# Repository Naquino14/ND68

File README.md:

# ND68
**ND68 MKL (Most keyless) Proto**

ND68 is a quest to design a custom 68% keyboard pcb powered by an RP2040, complete with per key RGB, hot-swappable keys, and a USB-C connector. 
We are in the prototyping phase, and if successful the prototype works as a macro pad.

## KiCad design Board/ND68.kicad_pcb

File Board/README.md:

# License for all subfolders of this one:

All files in subfolders of this one created by contrubutors of this repository are licensed under Creative Commons Attribution-NonCommercial-NoDerivatives (CC BY-NC-ND).

[Please view the license file here](LICENSE).

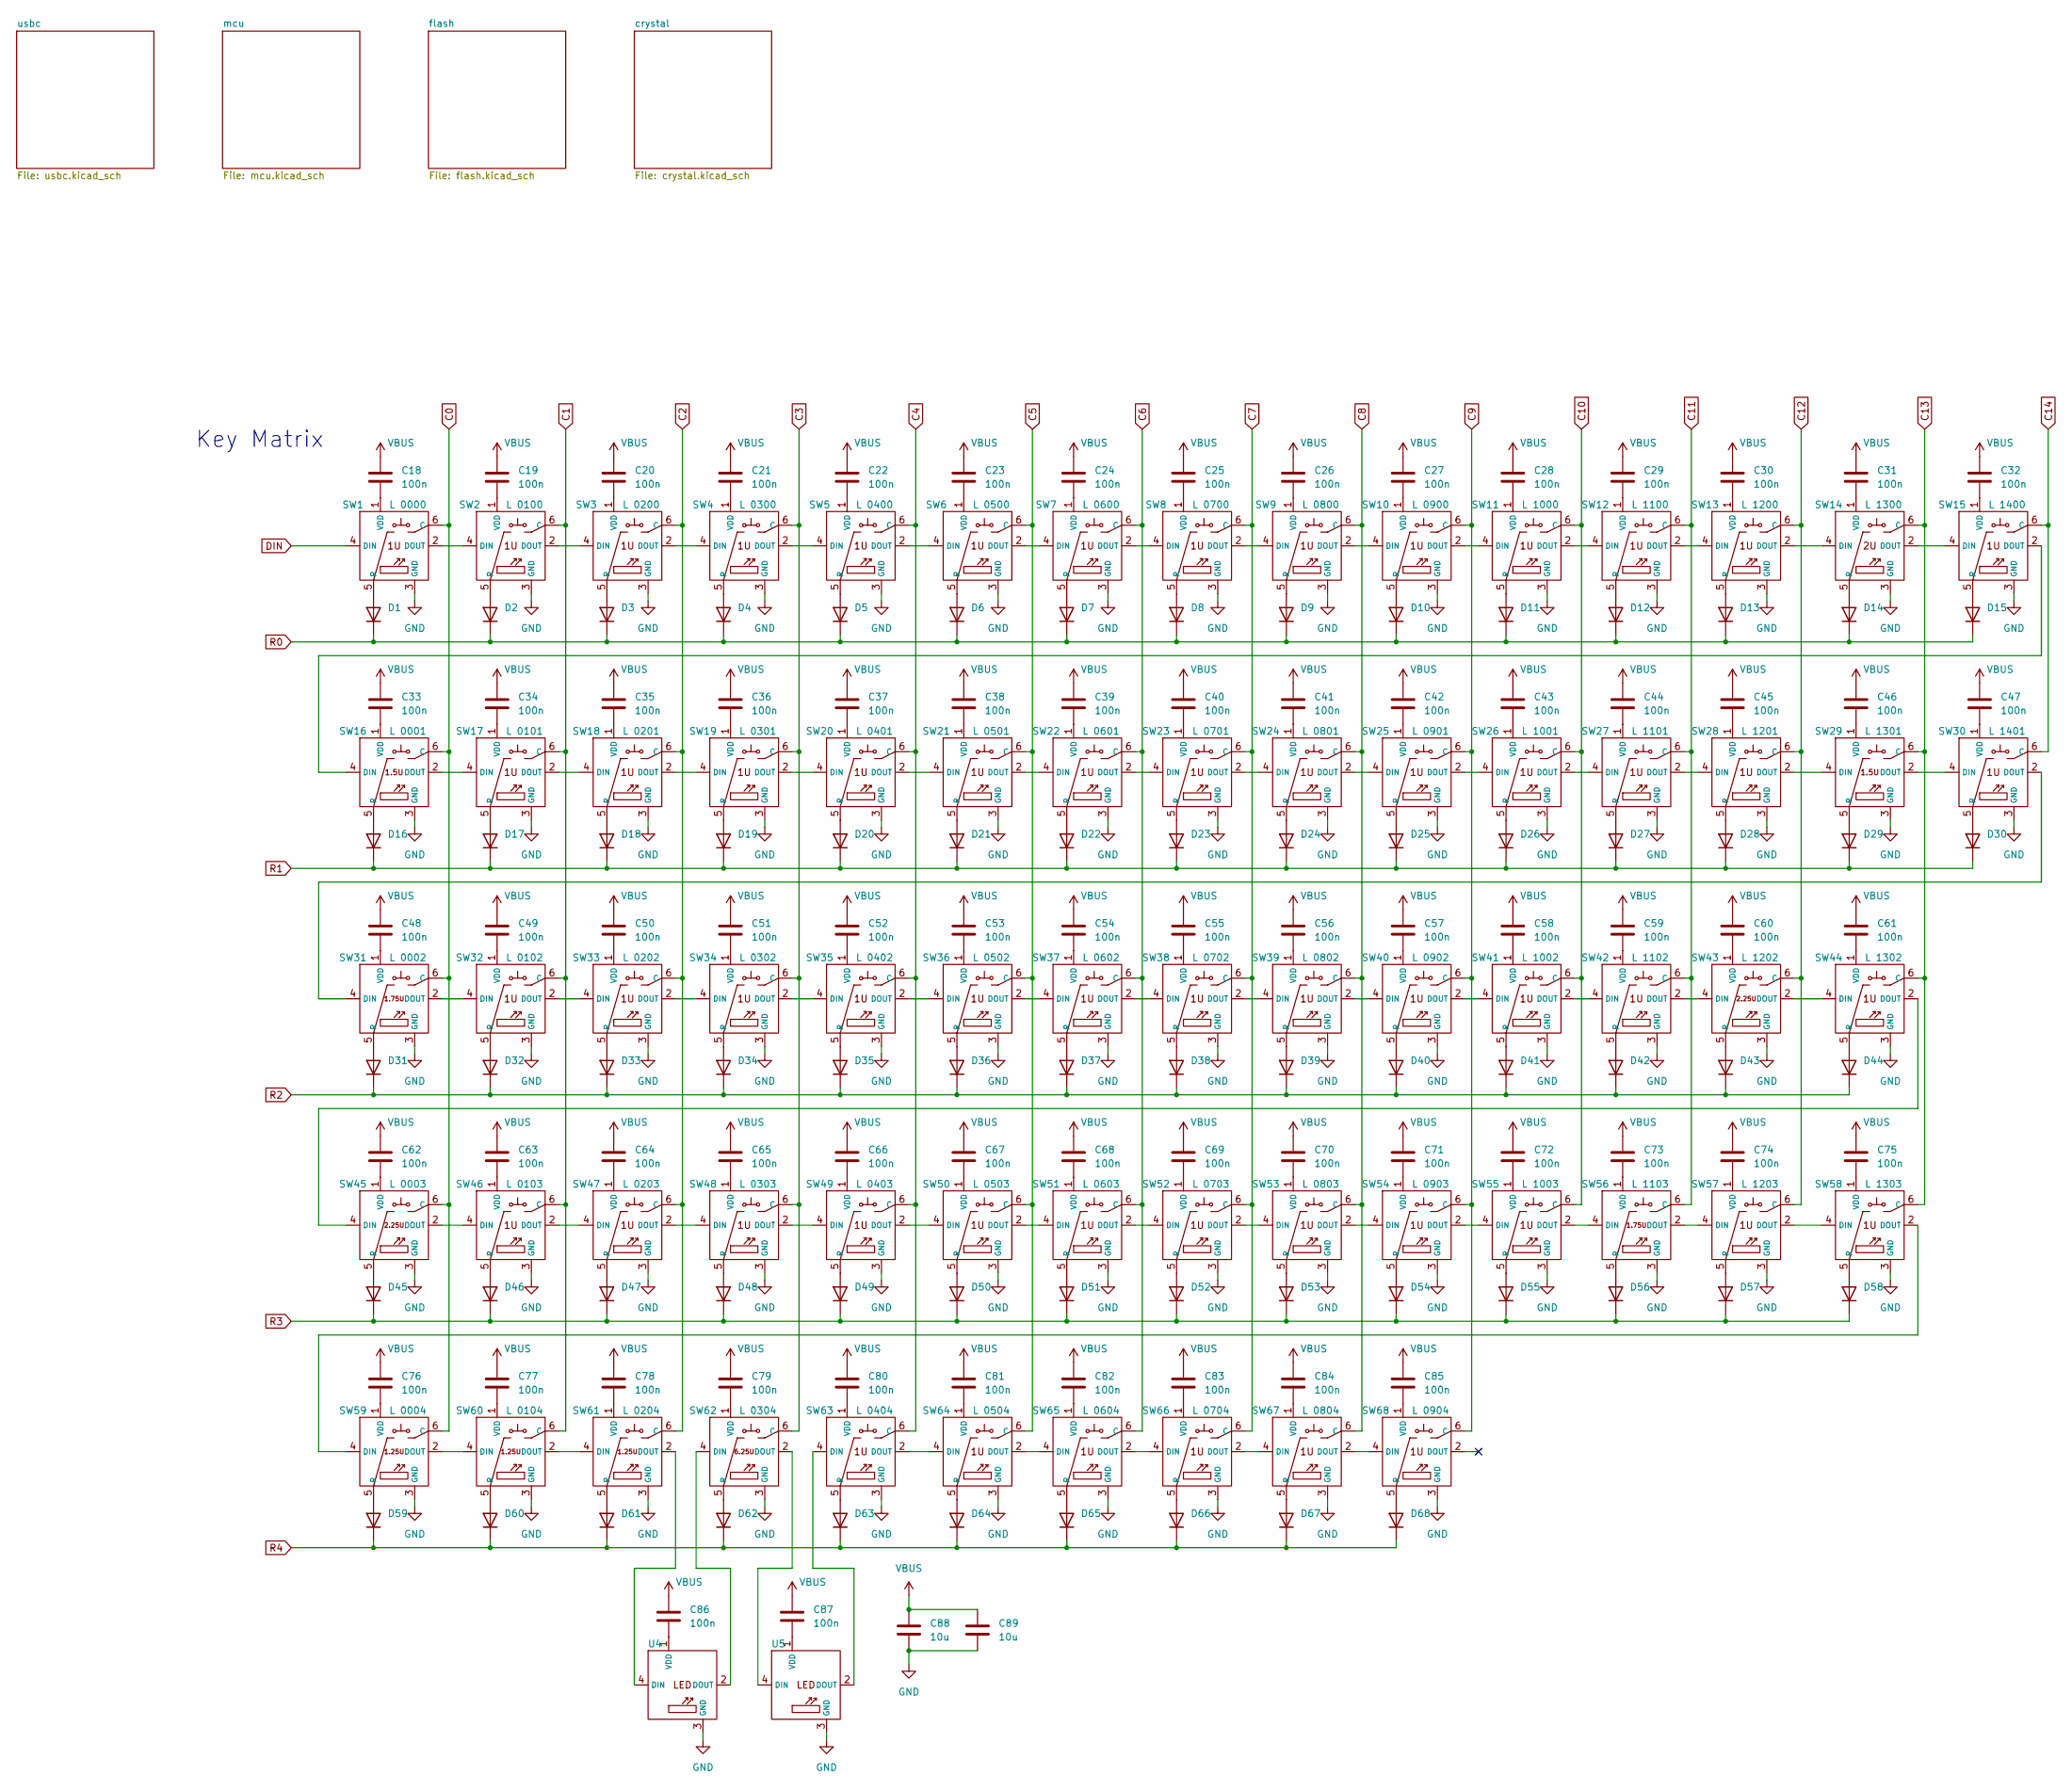
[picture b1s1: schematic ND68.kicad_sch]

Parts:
C18, C19, C20, C21, C22, C23, C24, C25, C26, C27, C28, C29, C30, C31, C32, C33, C34, C35, C36, C37, C38, C39, C40, C41, C42, C43, C44, C45, C46, C47, C48, C49, C50, C51, C52, C53, C54, C55, C56, C57, C58, C59, C60, C61, C62, C63, C64, C65, C66, C67, C68, C69, C70, C71, C72, C73, C74, C75, C76, C77, C78, C79, C80, C81, C82, C83, C84, C85, C86, C87: 100n; C_0603_1608Metric; DigiKey 311-1088-2-ND
C88, C89: 10u; C_0805_2012Metric; DigiKey 1276-1096-1-ND
D1, D2, D3, D4, D5, D6, D7, D8, D9, D10, D11, D12, D13, D14, D15, D16, D17, D18, D19, D20, D21, D22, D23, D24, D25, D26, D27, D28, D29, D30, D31, D32, D33, D34, D35, D36, D37, D38, D39, D40, D41, D42, D43, D44, D45, D46, D47, D48, D49, D50, D51, D52, D53, D54, D55, D56, D57, D58, D59, D60, D61, D62, D63, D64, D65, D66, D67, D68: D; D_SOD-123F; DigiKey 4878-1N4148WCT-ND
SW1, SW2, SW3, SW4, SW5, SW6, SW7, SW8, SW9, SW10, SW11, SW12, SW13, SW15, SW17, SW18, SW19, SW20, SW21, SW22, SW23, SW24, SW25, SW26, SW27, SW28, SW30, SW32, SW33, SW34, SW35, SW36, SW37, SW38, SW39, SW40, SW41, SW42, SW44, SW46, SW47, SW48, SW49, SW50, SW51, SW52, SW53, SW54, SW55, SW57, SW58, SW63, SW64, SW65, SW66, SW67, SW68: ND68-1U-HS-ARGB
SW14: ND68-2U-HS-ARGB
SW16, SW29: ND68-1.5U-HS-ARGB
SW31, SW56: ND68-1.75U-HS-ARGB
SW43, SW45: ND68-2.25U-HS-ARGB
SW59, SW60, SW61: ND68-1.25U-HS-ARGB
SW62: ND68-6.25U-HS-ARGB
U4, U5: ND68-1U-ARGB_LED_ONLY

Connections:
C0: SW1.6 (C), SW16.6 (C), SW31.6 (C), SW45.6 (C), SW59.6 (C)
C1: SW2.6 (C), SW17.6 (C), SW32.6 (C), SW46.6 (C), SW60.6 (C)
C2: SW3.6 (C), SW18.6 (C), SW33.6 (C), SW47.6 (C), SW61.6 (C)
C3: SW4.6 (C), SW19.6 (C), SW34.6 (C), SW48.6 (C), SW62.6 (C)
C4: SW5.6 (C), SW20.6 (C), SW35.6 (C), SW49.6 (C), SW63.6 (C)
C5: SW6.6 (C), SW21.6 (C), SW36.6 (C), SW50.6 (C), SW64.6 (C)
C6: SW7.6 (C), SW22.6 (C), SW37.6 (C), SW51.6 (C), SW65.6 (C)
C7: SW8.6 (C), SW23.6 (C), SW38.6 (C), SW52.6 (C), SW66.6 (C)
C8: SW9.6 (C), SW24.6 (C), SW39.6 (C), SW53.6 (C), SW67.6 (C)
C9: SW10.6 (C), SW25.6 (C), SW40.6 (C), SW54.6 (C), SW68.6 (C)
C10: SW11.6 (C), SW26.6 (C), SW41.6 (C), SW55.6 (C)
C11: SW12.6 (C), SW27.6 (C), SW42.6 (C), SW56.6 (C)
C12: SW13.6 (C), SW28.6 (C), SW43.6 (C), SW57.6 (C)
C13: SW14.6 (C), SW29.6 (C), SW44.6 (C), SW58.6 (C)
C14: SW15.6 (C), SW30.6 (C)
DIN: SW1.4 (DIN); also elsewhere on the board
GND: C88.2, C89.2, SW1.3 (GND), SW2.3 (GND), SW3.3 (GND), SW4.3 (GND), SW5.3 (GND), SW6.3 (GND), SW7.3 (GND), SW8.3 (GND), SW9.3 (GND), SW10.3 (GND), SW11.3 (GND), SW12.3 (GND), SW13.3 (GND), SW14.3 (GND), SW15.3 (GND), SW16.3 (GND), SW17.3 (GND), SW18.3 (GND), SW19.3 (GND), SW20.3 (GND), SW21.3 (GND), SW22.3 (GND), SW23.3 (GND), SW24.3 (GND), SW25.3 (GND), SW26.3 (GND), SW27.3 (GND), SW28.3 (GND), SW29.3 (GND), SW30.3 (GND), SW31.3 (GND), SW32.3 (GND), SW33.3 (GND), SW34.3 (GND), SW35.3 (GND), SW36.3 (GND), SW37.3 (GND), SW38.3 (GND), SW39.3 (GND), SW40.3 (GND), SW41.3 (GND), SW42.3 (GND), SW43.3 (GND), SW44.3 (GND), SW45.3 (GND), SW46.3 (GND), SW47.3 (GND), SW48.3 (GND), SW49.3 (GND), SW50.3 (GND), SW51.3 (GND), SW52.3 (GND), SW53.3 (GND), SW54.3 (GND), SW55.3 (GND), SW56.3 (GND), SW57.3 (GND), SW58.3 (GND), SW59.3 (GND), SW60.3 (GND), SW61.3 (GND), SW62.3 (GND), SW63.3 (GND), SW64.3 (GND), SW65.3 (GND), SW66.3 (GND), SW67.3 (GND), SW68.3 (GND), U4.3 (GND), U5.3 (GND); also elsewhere on the board
unnamed: D1.2 (A), SW1.5 (R)
unnamed: D2.2 (A), SW2.5 (R)
unnamed: D3.2 (A), SW3.5 (R)
unnamed: D4.2 (A), SW4.5 (R)
unnamed: D5.2 (A), SW5.5 (R)
unnamed: D6.2 (A), SW6.5 (R)
unnamed: D7.2 (A), SW7.5 (R)
unnamed: D8.2 (A), SW8.5 (R)
unnamed: D9.2 (A), SW9.5 (R)
unnamed: D10.2 (A), SW10.5 (R)
unnamed: D11.2 (A), SW11.5 (R)
unnamed: D12.2 (A), SW12.5 (R)
unnamed: D13.2 (A), SW13.5 (R)
unnamed: D14.2 (A), SW14.5 (R)
unnamed: D15.2 (A), SW15.5 (R)
unnamed: D16.2 (A), SW16.5 (R)
unnamed: D17.2 (A), SW17.5 (R)
unnamed: D18.2 (A), SW18.5 (R)
unnamed: D19.2 (A), SW19.5 (R)
unnamed: D20.2 (A), SW20.5 (R)
unnamed: D21.2 (A), SW21.5 (R)
unnamed: D22.2 (A), SW22.5 (R)
unnamed: D23.2 (A), SW23.5 (R)
unnamed: D24.2 (A), SW24.5 (R)
unnamed: D25.2 (A), SW25.5 (R)
unnamed: D26.2 (A), SW26.5 (R)
unnamed: D27.2 (A), SW27.5 (R)
unnamed: D28.2 (A), SW28.5 (R)
unnamed: D29.2 (A), SW29.5 (R)
unnamed: D30.2 (A), SW30.5 (R)
unnamed: D31.2 (A), SW31.5 (R)
unnamed: D32.2 (A), SW32.5 (R)
unnamed: D33.2 (A), SW33.5 (R)
unnamed: D34.2 (A), SW34.5 (R)
unnamed: D35.2 (A), SW35.5 (R)
unnamed: D36.2 (A), SW36.5 (R)
unnamed: D37.2 (A), SW37.5 (R)
unnamed: D38.2 (A), SW38.5 (R)
unnamed: D39.2 (A), SW39.5 (R)
unnamed: D40.2 (A), SW40.5 (R)
unnamed: D41.2 (A), SW41.5 (R)
unnamed: D42.2 (A), SW42.5 (R)
unnamed: D43.2 (A), SW43.5 (R)
unnamed: D44.2 (A), SW44.5 (R)
unnamed: D45.2 (A), SW45.5 (R)
unnamed: D46.2 (A), SW46.5 (R)
unnamed: D47.2 (A), SW47.5 (R)
unnamed: D48.2 (A), SW48.5 (R)
unnamed: D49.2 (A), SW49.5 (R)
unnamed: D50.2 (A), SW50.5 (R)
unnamed: D51.2 (A), SW51.5 (R)
unnamed: D52.2 (A), SW52.5 (R)
unnamed: D53.2 (A), SW53.5 (R)
unnamed: D54.2 (A), SW54.5 (R)
unnamed: D55.2 (A), SW55.5 (R)
unnamed: D56.2 (A), SW56.5 (R)
unnamed: D57.2 (A), SW57.5 (R)
unnamed: D58.2 (A), SW58.5 (R)
unnamed: D59.2 (A), SW59.5 (R)
unnamed: D60.2 (A), SW60.5 (R)
unnamed: D61.2 (A), SW61.5 (R)
unnamed: D62.2 (A), SW62.5 (R)
unnamed: D63.2 (A), SW63.5 (R)
unnamed: D64.2 (A), SW64.5 (R)
unnamed: D65.2 (A), SW65.5 (R)
unnamed: D66.2 (A), SW66.5 (R)
unnamed: D67.2 (A), SW67.5 (R)
unnamed: D68.2 (A), SW68.5 (R)
unnamed: SW1.2 (DOUT), SW2.4 (DIN)
unnamed: C18.2, SW1.1 (VDD)
unnamed: SW2.2 (DOUT), SW3.4 (DIN)
unnamed: C19.2, SW2.1 (VDD)
unnamed: SW3.2 (DOUT), SW4.4 (DIN)
unnamed: C20.2, SW3.1 (VDD)
unnamed: SW4.2 (DOUT), SW5.4 (DIN)
unnamed: C21.2, SW4.1 (VDD)
unnamed: SW5.2 (DOUT), SW6.4 (DIN)
unnamed: C22.2, SW5.1 (VDD)
unnamed: SW6.2 (DOUT), SW7.4 (DIN)
unnamed: C23.2, SW6.1 (VDD)
unnamed: SW7.2 (DOUT), SW8.4 (DIN)
unnamed: C24.2, SW7.1 (VDD)
unnamed: SW8.2 (DOUT), SW9.4 (DIN)
unnamed: C25.2, SW8.1 (VDD)
unnamed: C26.2, SW9.1 (VDD)
unnamed: SW9.2 (DOUT), SW10.4 (DIN)
unnamed: SW10.2 (DOUT), SW11.4 (DIN)
unnamed: C27.2, SW10.1 (VDD)
unnamed: SW11.2 (DOUT), SW12.4 (DIN)
unnamed: C28.2, SW11.1 (VDD)
unnamed: SW12.2 (DOUT), SW13.4 (DIN)
unnamed: C29.2, SW12.1 (VDD)
unnamed: SW13.2 (DOUT), SW14.4 (DIN)
unnamed: C30.2, SW13.1 (VDD)
unnamed: SW14.2 (DOUT), SW15.4 (DIN)
unnamed: C31.2, SW14.1 (VDD)
unnamed: SW15.2 (DOUT), SW16.4 (DIN)
unnamed: C32.2, SW15.1 (VDD)
unnamed: SW16.2 (DOUT), SW17.4 (DIN)
unnamed: C33.2, SW16.1 (VDD)
unnamed: SW17.2 (DOUT), SW18.4 (DIN)
unnamed: C34.2, SW17.1 (VDD)
unnamed: SW18.2 (DOUT), SW19.4 (DIN)
unnamed: C35.2, SW18.1 (VDD)
unnamed: SW19.2 (DOUT), SW20.4 (DIN)
unnamed: C36.2, SW19.1 (VDD)
unnamed: SW20.2 (DOUT), SW21.4 (DIN)
unnamed: C37.2, SW20.1 (VDD)
unnamed: SW21.2 (DOUT), SW22.4 (DIN)
unnamed: C38.2, SW21.1 (VDD)
unnamed: SW22.2 (DOUT), SW23.4 (DIN)
unnamed: C39.2, SW22.1 (VDD)
unnamed: SW23.2 (DOUT), SW24.4 (DIN)
unnamed: C40.2, SW23.1 (VDD)
unnamed: SW24.2 (DOUT), SW25.4 (DIN)
unnamed: C41.2, SW24.1 (VDD)
unnamed: SW25.2 (DOUT), SW26.4 (DIN)
unnamed: C42.2, SW25.1 (VDD)
unnamed: SW26.2 (DOUT), SW27.4 (DIN)
unnamed: C43.2, SW26.1 (VDD)
unnamed: SW27.2 (DOUT), SW28.4 (DIN)
unnamed: C44.2, SW27.1 (VDD)
unnamed: SW28.2 (DOUT), SW29.4 (DIN)
unnamed: C45.2, SW28.1 (VDD)
unnamed: SW29.2 (DOUT), SW30.4 (DIN)
unnamed: C46.2, SW29.1 (VDD)
unnamed: SW30.2 (DOUT), SW31.4 (DIN)
unnamed: C47.2, SW30.1 (VDD)
unnamed: SW31.2 (DOUT), SW32.4 (DIN)
unnamed: C48.2, SW31.1 (VDD)
unnamed: SW32.2 (DOUT), SW33.4 (DIN)
unnamed: C49.2, SW32.1 (VDD)
unnamed: SW33.2 (DOUT), SW34.4 (DIN)
unnamed: C50.2, SW33.1 (VDD)
unnamed: SW34.2 (DOUT), SW35.4 (DIN)
unnamed: C51.2, SW34.1 (VDD)
unnamed: SW35.2 (DOUT), SW36.4 (DIN)
unnamed: C52.2, SW35.1 (VDD)
unnamed: SW36.2 (DOUT), SW37.4 (DIN)
unnamed: C53.2, SW36.1 (VDD)
unnamed: SW37.2 (DOUT), SW38.4 (DIN)
unnamed: C54.2, SW37.1 (VDD)
unnamed: SW38.2 (DOUT), SW39.4 (DIN)
unnamed: C55.2, SW38.1 (VDD)
unnamed: SW39.2 (DOUT), SW40.4 (DIN)
unnamed: C56.2, SW39.1 (VDD)
unnamed: SW40.2 (DOUT), SW41.4 (DIN)
unnamed: C57.2, SW40.1 (VDD)
unnamed: SW41.2 (DOUT), SW42.4 (DIN)
unnamed: C58.2, SW41.1 (VDD)
unnamed: SW42.2 (DOUT), SW43.4 (DIN)
unnamed: C59.2, SW42.1 (VDD)
unnamed: SW43.2 (DOUT), SW44.4 (DIN)
unnamed: C60.2, SW43.1 (VDD)
unnamed: SW44.2 (DOUT), SW45.4 (DIN)
unnamed: C61.2, SW44.1 (VDD)
unnamed: SW45.2 (DOUT), SW46.4 (DIN)
unnamed: C62.2, SW45.1 (VDD)
unnamed: SW46.2 (DOUT), SW47.4 (DIN)
unnamed: C63.2, SW46.1 (VDD)
unnamed: SW47.2 (DOUT), SW48.4 (DIN)
unnamed: C64.2, SW47.1 (VDD)
unnamed: SW48.2 (DOUT), SW49.4 (DIN)
unnamed: C65.2, SW48.1 (VDD)
unnamed: SW49.2 (DOUT), SW50.4 (DIN)
unnamed: C66.2, SW49.1 (VDD)
unnamed: SW50.2 (DOUT), SW51.4 (DIN)
unnamed: C67.2, SW50.1 (VDD)
unnamed: SW51.2 (DOUT), SW52.4 (DIN)
unnamed: C68.2, SW51.1 (VDD)
unnamed: SW52.2 (DOUT), SW53.4 (DIN)
unnamed: C69.2, SW52.1 (VDD)
unnamed: SW53.2 (DOUT), SW54.4 (DIN)
unnamed: C70.2, SW53.1 (VDD)
unnamed: SW54.2 (DOUT), SW55.4 (DIN)
unnamed: C71.2, SW54.1 (VDD)
unnamed: SW55.2 (DOUT), SW56.4 (DIN)
unnamed: C72.2, SW55.1 (VDD)
unnamed: SW56.2 (DOUT), SW57.4 (DIN)
unnamed: C73.2, SW56.1 (VDD)
unnamed: SW57.2 (DOUT), SW58.4 (DIN)
unnamed: C74.2, SW57.1 (VDD)
unnamed: SW58.2 (DOUT), SW59.4 (DIN)
unnamed: C75.2, SW58.1 (VDD)
unnamed: SW59.2 (DOUT), SW60.4 (DIN)
unnamed: C76.2, SW59.1 (VDD)
unnamed: SW60.2 (DOUT), SW61.4 (DIN)
unnamed: C77.2, SW60.1 (VDD)
unnamed: SW61.2 (DOUT), U4.4 (DIN)
unnamed: C78.2, SW61.1 (VDD)
unnamed: SW62.4 (DIN), U4.2 (DOUT)
unnamed: SW62.2 (DOUT), U5.4 (DIN)
unnamed: C79.2, SW62.1 (VDD)
unnamed: SW63.4 (DIN), U5.2 (DOUT)
unnamed: SW63.2 (DOUT), SW64.4 (DIN)
unnamed: C80.2, SW63.1 (VDD)
unnamed: SW64.2 (DOUT), SW65.4 (DIN)
unnamed: C81.2, SW64.1 (VDD)
unnamed: SW65.2 (DOUT), SW66.4 (DIN)
unnamed: C82.2, SW65.1 (VDD)
unnamed: SW66.2 (DOUT), SW67.4 (DIN)
unnamed: C83.2, SW66.1 (VDD)
unnamed: SW67.2 (DOUT), SW68.4 (DIN)
unnamed: C84.2, SW67.1 (VDD)
unnamed: C85.2, SW68.1 (VDD)
unnamed: C86.2, U4.1 (VDD)
unnamed: C87.2, U5.1 (VDD)
R0: D1.1 (K), D2.1 (K), D3.1 (K), D4.1 (K), D5.1 (K), D6.1 (K), D7.1 (K), D8.1 (K), D9.1 (K), D10.1 (K), D11.1 (K), D12.1 (K), D13.1 (K), D14.1 (K), D15.1 (K)
R1: D16.1 (K), D17.1 (K), D18.1 (K), D19.1 (K), D20.1 (K), D21.1 (K), D22.1 (K), D23.1 (K), D24.1 (K), D25.1 (K), D26.1 (K), D27.1 (K), D28.1 (K), D29.1 (K), D30.1 (K)
R2: D31.1 (K), D32.1 (K), D33.1 (K), D34.1 (K), D35.1 (K), D36.1 (K), D37.1 (K), D38.1 (K), D39.1 (K), D40.1 (K), D41.1 (K), D42.1 (K), D43.1 (K), D44.1 (K)
R3: D45.1 (K), D46.1 (K), D47.1 (K), D48.1 (K), D49.1 (K), D50.1 (K), D51.1 (K), D52.1 (K), D53.1 (K), D54.1 (K), D55.1 (K), D56.1 (K), D57.1 (K), D58.1 (K)
R4: D59.1 (K), D60.1 (K), D61.1 (K), D62.1 (K), D63.1 (K), D64.1 (K), D65.1 (K), D66.1 (K), D67.1 (K), D68.1 (K)
VBUS: C18.1, C19.1, C20.1, C21.1, C22.1, C23.1, C24.1, C25.1, C26.1, C27.1, C28.1, C29.1, C30.1, C31.1, C32.1, C33.1, C34.1, C35.1, C36.1, C37.1, C38.1, C39.1, C40.1, C41.1, C42.1, C43.1, C44.1, C45.1, C46.1, C47.1, C48.1, C49.1, C50.1, C51.1, C52.1, C53.1, C54.1, C55.1, C56.1, C57.1, C58.1, C59.1, C60.1, C61.1, C62.1, C63.1, C64.1, C65.1, C66.1, C67.1, C68.1, C69.1, C70.1, C71.1, C72.1, C73.1, C74.1, C75.1, C76.1, C77.1, C78.1, C79.1, C80.1, C81.1, C82.1, C83.1, C84.1, C85.1, C86.1, C87.1, C88.1, C89.1; also elsewhere on the board

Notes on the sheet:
Key Matrix

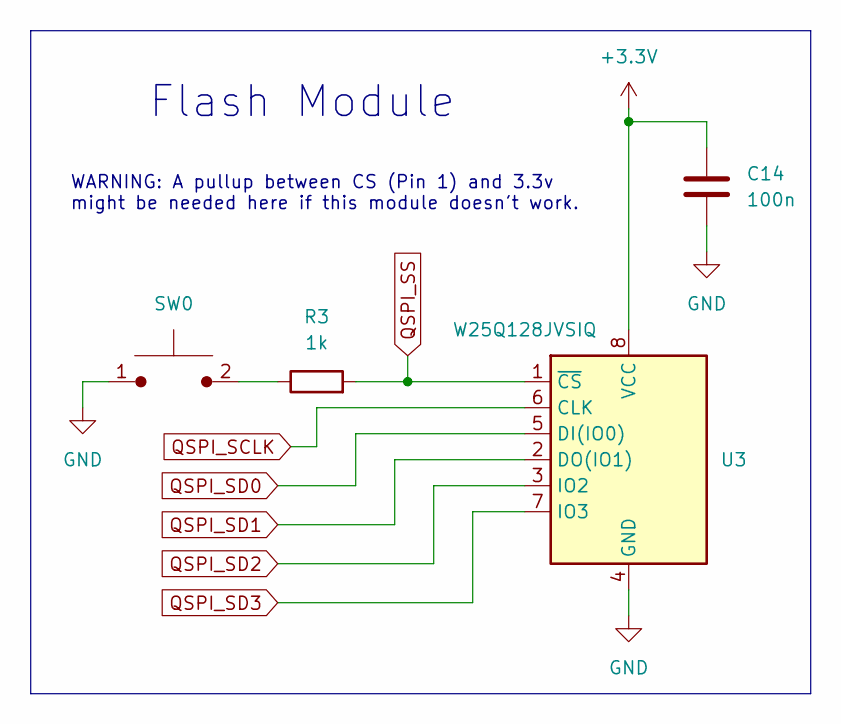
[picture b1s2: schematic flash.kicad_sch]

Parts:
C14: 100n; C_0201_0603Metric; DigiKey 1276-1013-1-ND
R3: 1k; R_0402_1005Metric; DigiKey 311-1.0KJRCT-ND
SW0: PTS636 SM43 SMTR LFS; DigiKey CKN12310-1-ND
U3: W25Q128JVSIQ; DigiKey W25Q128JVSIQ-ND

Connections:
+3.3V: C14.1, U3.8 (VCC); also elsewhere on the board
GND: C14.2, SW0.1, U3.4 (GND); also elsewhere on the board
unnamed: R3.1, SW0.2
QSPI_SCLK: U3.6 (CLK); also elsewhere on the board
QSPI_SD0: U3.5 (DI(IO0)); also elsewhere on the board
QSPI_SD1: U3.2 (DO(IO1)); also elsewhere on the board
QSPI_SD2: U3.3 (IO2); also elsewhere on the board
QSPI_SD3: U3.7 (IO3); also elsewhere on the board
QSPI_SS: R3.2, U3.1 (~CS); also elsewhere on the board

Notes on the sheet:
Flash Module
WARNING: A pullup between CS (Pin 1) and 3.3v might be needed here if this module doesn't work.

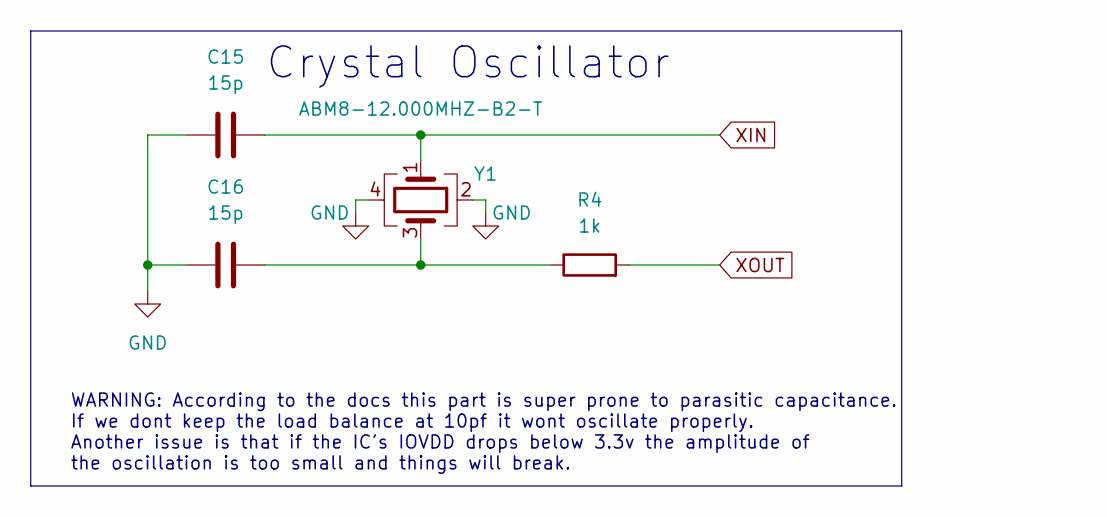
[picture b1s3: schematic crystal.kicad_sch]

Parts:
C15, C16: 15p; C_0201_0603Metric; DigiKey 490-9658-1-ND
R4: 1k; R_0402_1005Metric; DigiKey 311-1.0KJRCT-ND
Y1: Crystal_GND24; XTAL_ABM8-12.000MHZ-B2-T; DigiKey 535-9826-1-ND

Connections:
GND: C15.1, C16.1, Y1.2, Y1.4; also elsewhere on the board
unnamed: C16.2, R4.1, Y1.3
XIN: C15.2, Y1.1; also elsewhere on the board
XOUT: R4.2; also elsewhere on the board

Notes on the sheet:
WARNING: According to the docs this part is super prone to parasitic capacitance. If we dont keep the load balance at 10pf it wont oscillate properly. Another issue is that if the IC's IOVDD drops below 3.3v the amplitude of the oscillation is too small and things will break.
Crystal Oscillator

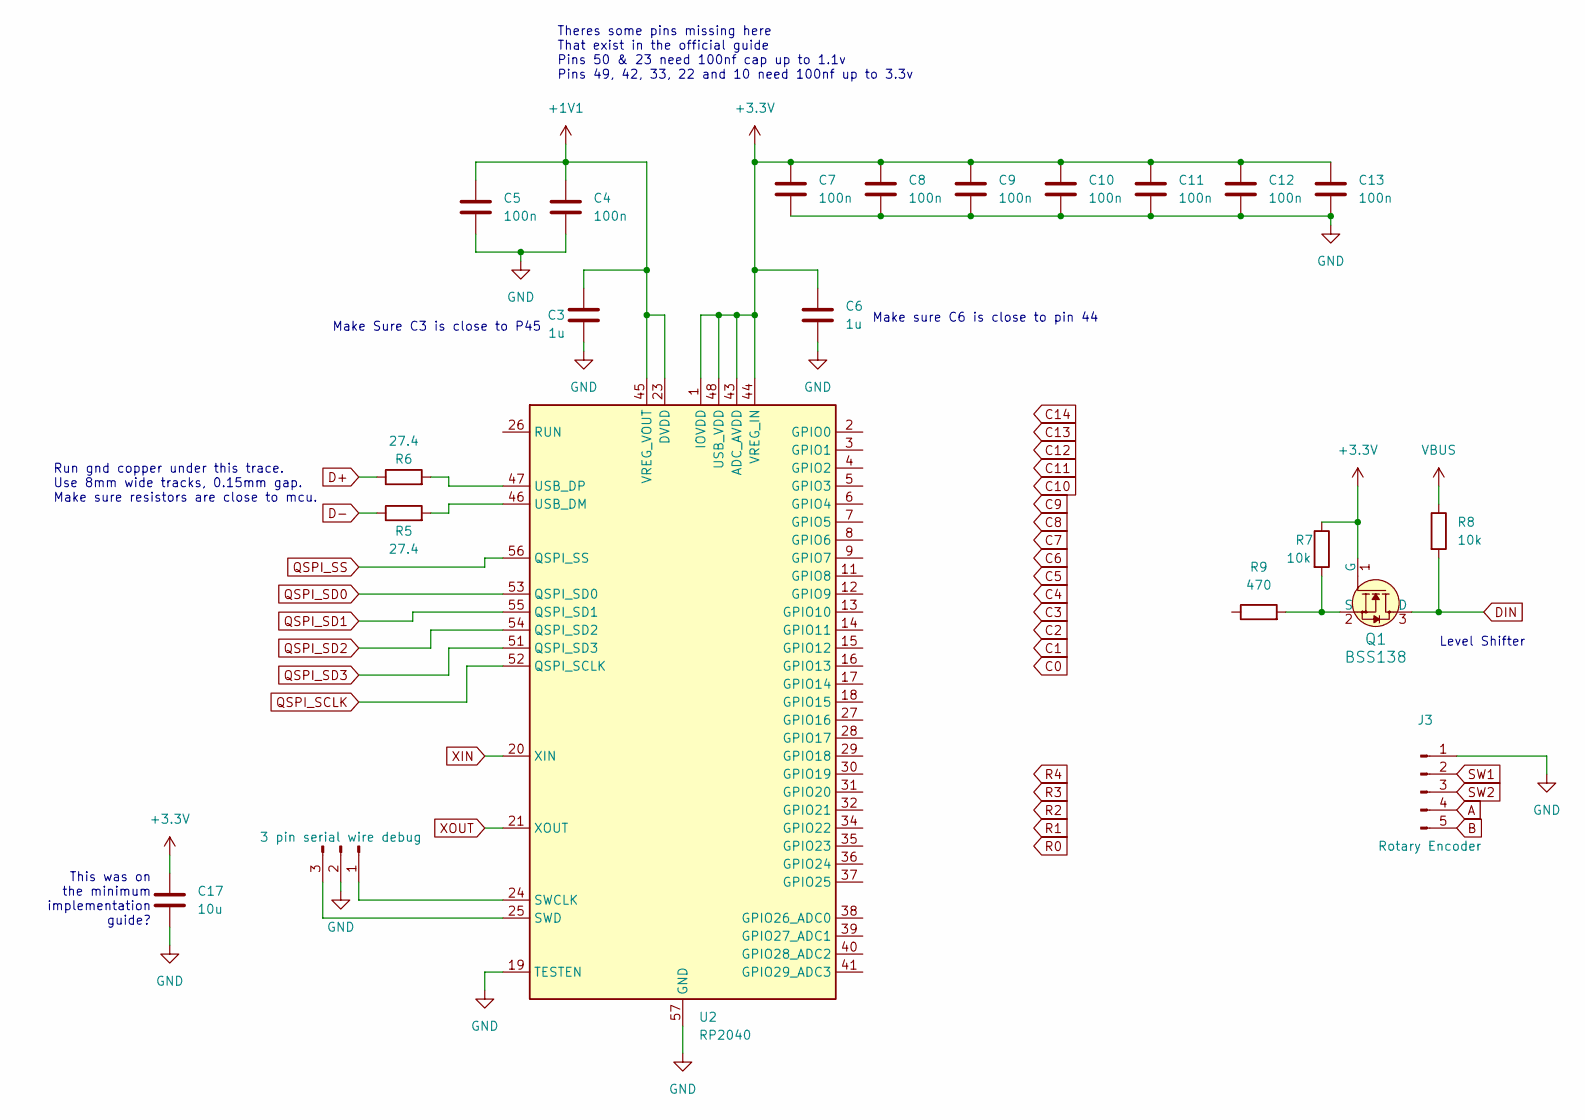
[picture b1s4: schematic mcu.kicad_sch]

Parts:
C3, C6: 1u; C_0402_1005Metric; DigiKey 490-13339-1-ND
C4, C5, C7, C8, C9, C10, C11, C12, C13: 100n; C_0201_0603Metric; DigiKey 1276-1013-1-ND
C17: 10u; C_0805_2012Metric; DigiKey 1276-1096-1-ND
J2: Conn_01x03_Pin; PinHeader_1x03_P2.54mm_Vertical
J3: Conn_01x05_Pin; PinHeader_1x05_P2.54mm_Vertical
Q1: BSS138; SOT-23-3; MPN BSS138; Digi-Key_PN BSS138CT-ND
R5, R6: 27.4; R_0402_1005Metric; DigiKey YAG3085CT-ND
R7, R8: 10k; R_0402_1005Metric; DigiKey 311-10KJRTR-ND
R9: 470; R_0603_1608Metric; DigiKey P470DBTR-ND
U2: RP2040; QFN-56-1EP_7x7mm_P0.4mm_EP3.2x3.2mm

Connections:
+1V1: C3.1, C4.1, C5.1, U2.23 (DVDD), U2.45 (VREG_VOUT), U2.50 (DVDD)
+3.3V: C6.1, C7.1, C8.1, C9.1, C10.1, C11.1, C12.1, C13.1, C17.1, Q1.1 (G), R7.1, U2.1 (IOVDD), U2.10 (IOVDD), U2.22 (IOVDD), U2.33 (IOVDD), U2.42 (IOVDD), U2.43 (ADC_AVDD), U2.44 (VREG_IN), U2.48 (USB_VDD), U2.49 (IOVDD); also elsewhere on the board
A: J3.4
B: J3.5
D+: R6.1; also elsewhere on the board
D-: R5.1; also elsewhere on the board
DIN: Q1.3 (D), R8.2; also elsewhere on the board
GND: C3.2, C4.2, C5.2, C6.2, C7.2, C8.2, C9.2, C10.2, C11.2, C12.2, C13.2, C17.2, J2.2, J3.1, U2.19 (TESTEN), U2.57 (GND); also elsewhere on the board
unnamed: J2.1, U2.24 (SWCLK)
unnamed: J2.3, U2.25 (SWD)
unnamed: Q1.2 (S), R7.2, R9.2
unnamed: R5.2, U2.46 (USB_DM)
unnamed: R6.2, U2.47 (USB_DP)
QSPI_SCLK: U2.52 (QSPI_SCLK); also elsewhere on the board
QSPI_SD0: U2.53 (QSPI_SD0); also elsewhere on the board
QSPI_SD1: U2.55 (QSPI_SD1); also elsewhere on the board
QSPI_SD2: U2.54 (QSPI_SD2); also elsewhere on the board
QSPI_SD3: U2.51 (QSPI_SD3); also elsewhere on the board
QSPI_SS: U2.56 (QSPI_SS); also elsewhere on the board
SW1: J3.2
SW2: J3.3
VBUS: R8.1; also elsewhere on the board
XIN: U2.20 (XIN); also elsewhere on the board
XOUT: U2.21 (XOUT); also elsewhere on the board

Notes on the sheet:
Level Shifter
This was on the minimum implementation guide?
Make sure C6 is close to pin 44
Theres some pins missing here That exist in the official guide Pins 50 & 23 need 100nf cap up to 1.1v Pins 49, 42, 33, 22 and 10 need 100nf up to 3.3v
Run gnd copper under this trace. Use 8mm wide tracks, 0.15mm gap. Make sure resistors are close to mcu.
Make Sure C3 is close to P45

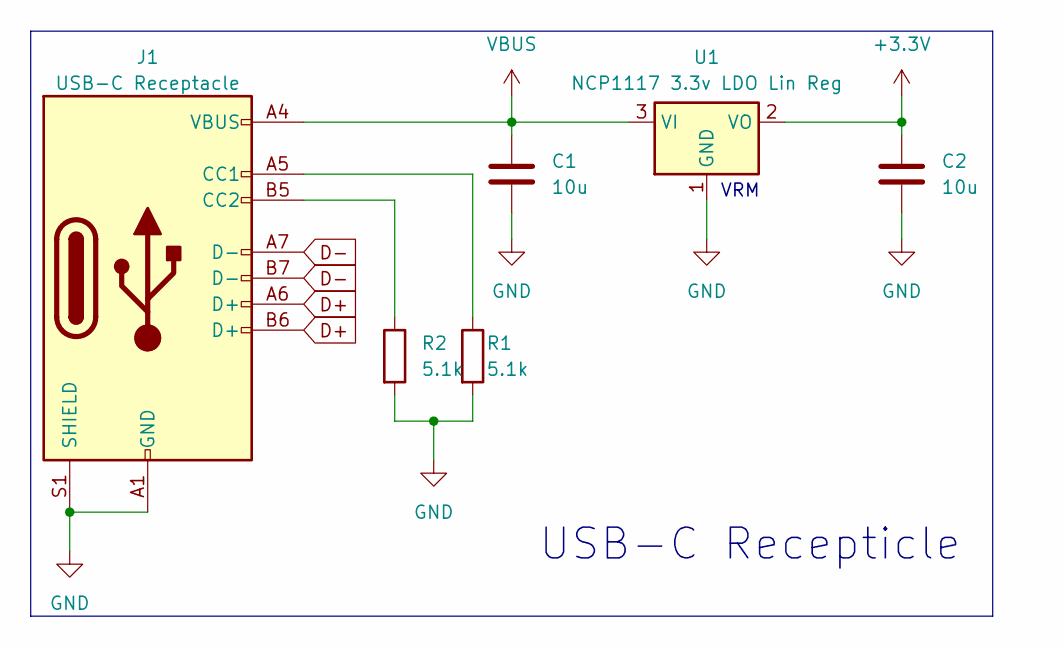
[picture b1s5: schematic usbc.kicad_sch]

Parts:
C1, C2: 10u; C_0805_2012Metric; DigiKey 1276-1096-1-ND
J1: USB_C_Receptacle_USB2.0_14P; USB_C_Receptacle_GCT_USB4105-GF-A; DigiKey 2073-USB4105-GF-ACT-ND
R1, R2: 5.1k; R_0603_1608Metric; DigiKey 311-5.10KHRCT-ND
U1: NCP1117-3.3_SOT223; SOT-223-3_TabPin2; DigiKey 488-NCP1117IST33T3GCT-ND

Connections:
+3.3V: C2.1, U1.2 (VO); also elsewhere on the board
D+: J1.A6 (D+), J1.B6 (D+); also elsewhere on the board
D-: J1.A7 (D-), J1.B7 (D-); also elsewhere on the board
GND: C1.2, C2.2, J1.A1 (GND), J1.A12 (GND), J1.B1 (GND), J1.B12 (GND), J1.S1 (SHIELD), R1.2, R2.2, U1.1 (GND); also elsewhere on the board
unnamed: J1.A5 (CC1), R1.1
unnamed: J1.B5 (CC2), R2.1
VBUS: C1.1, J1.A4 (VBUS), J1.A9 (VBUS), J1.B4 (VBUS), J1.B9 (VBUS), U1.3 (VI); also elsewhere on the board

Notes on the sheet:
VRM
USB-C Recepticle

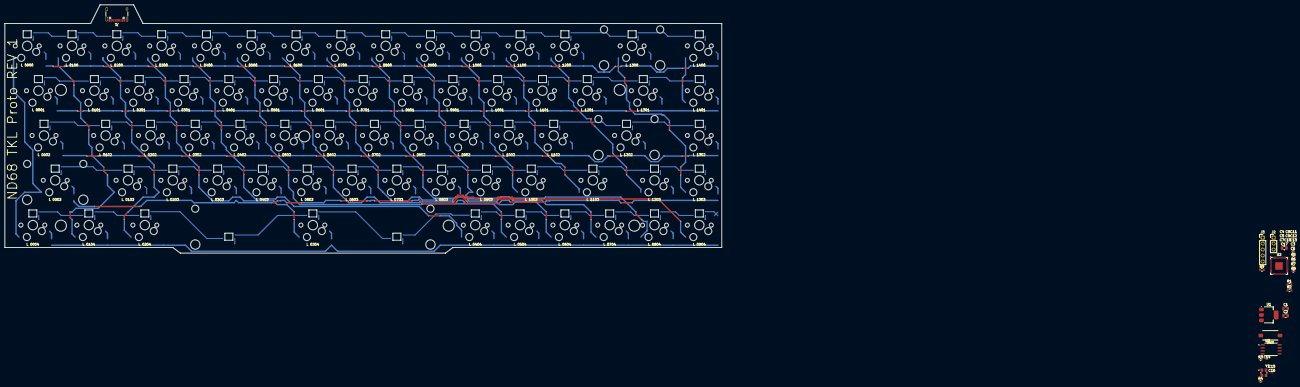
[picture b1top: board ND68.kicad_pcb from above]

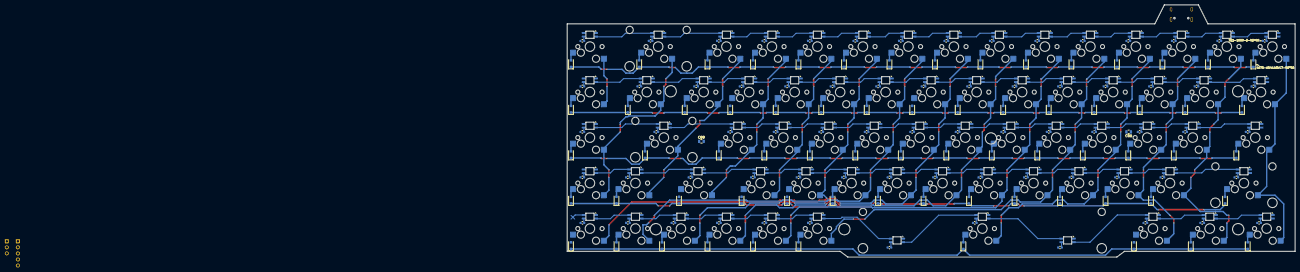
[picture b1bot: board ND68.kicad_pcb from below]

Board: 2 copper layers, 304.8 x 105.6 mm, 244 parts (140 on the bottom side), 251 nets.

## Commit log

2024-02-19 Create KiCad project
2024-02-19 Create LICENSE
2024-02-19 Create board license
2024-02-19 Create board license readme
2024-02-20 Created drawing for Key and ARGB led and basic 4x4 proto wiring
2024-02-21 Removed local-specific tables and update gitignore
2024-02-21 Added schematics, footprints, 3d models, and wiring to rp2040 input supply
2024-02-21 Added pulldowns to USBC Receptacle CC1 and CC2 pins
2024-02-22 renamed mcu sheet to usbc
2024-02-22 Added mcu power pin decoupling capacitors
2024-02-22 Finished Flash Storage
2024-02-22 Finished creating crystal oscillator
2024-02-22 Update board folder readme to have precise language.
2024-02-22 Touch-up module schematics
2024-02-23 Added the rest of the required stuff tp the mcu
2024-02-25 SK6812 rev mount led footprint
2024-02-27 Cleaned up key matrix and added diodes
2024-02-27 Added 3d model to ND68-1u-HS-ARGB and linked all parts to footprints
2024-02-27 WIP PCB Layout
2024-02-29 VERY BASIC pcb layout
2024-03-01 Fixed pad numbers on 1u argb hotswap footprint and added a border to the pcb :)
2024-03-01 Route mcu
2024-03-03 Done routing all parts.
2024-03-04 Update gitignore
2024-03-05 Fixed coupling issues and cleaned up board
2024-03-05 Ordered parts, upload BOM for 1 proto, 2 keyboards
2024-04-14 Rev 2
2024-04-29 MKL Rev 2 final
2024-04-29 65% ke matrix
2024-04-29 Added 2 leds
2024-04-30 Change led decoupler type
2024-04-30 Starting from scratch
2024-05-16 WIP Layout, all keys placed
2024-06-19 Finished PCB keyboard matrix & diodes
2024-06-19 Wire capacitors and wire up diode matrix
2024-07-21 Backing up"
2024-08-11 Finish routing key matrix
2024-08-11 Finish rev1
2024-08-11 Fix up board in accordance with JLCPCB DRC
2024-08-11 Forgot to add teardrops
2024-08-12 Finishing touches
2024-11-01 Backing up rev 1
2024-11-03 Columns, power, leds, and zones
2024-11-06 Wire most of rev2
2024-11-12 REV2 complete
2025-02-16 Rev 1 fix
